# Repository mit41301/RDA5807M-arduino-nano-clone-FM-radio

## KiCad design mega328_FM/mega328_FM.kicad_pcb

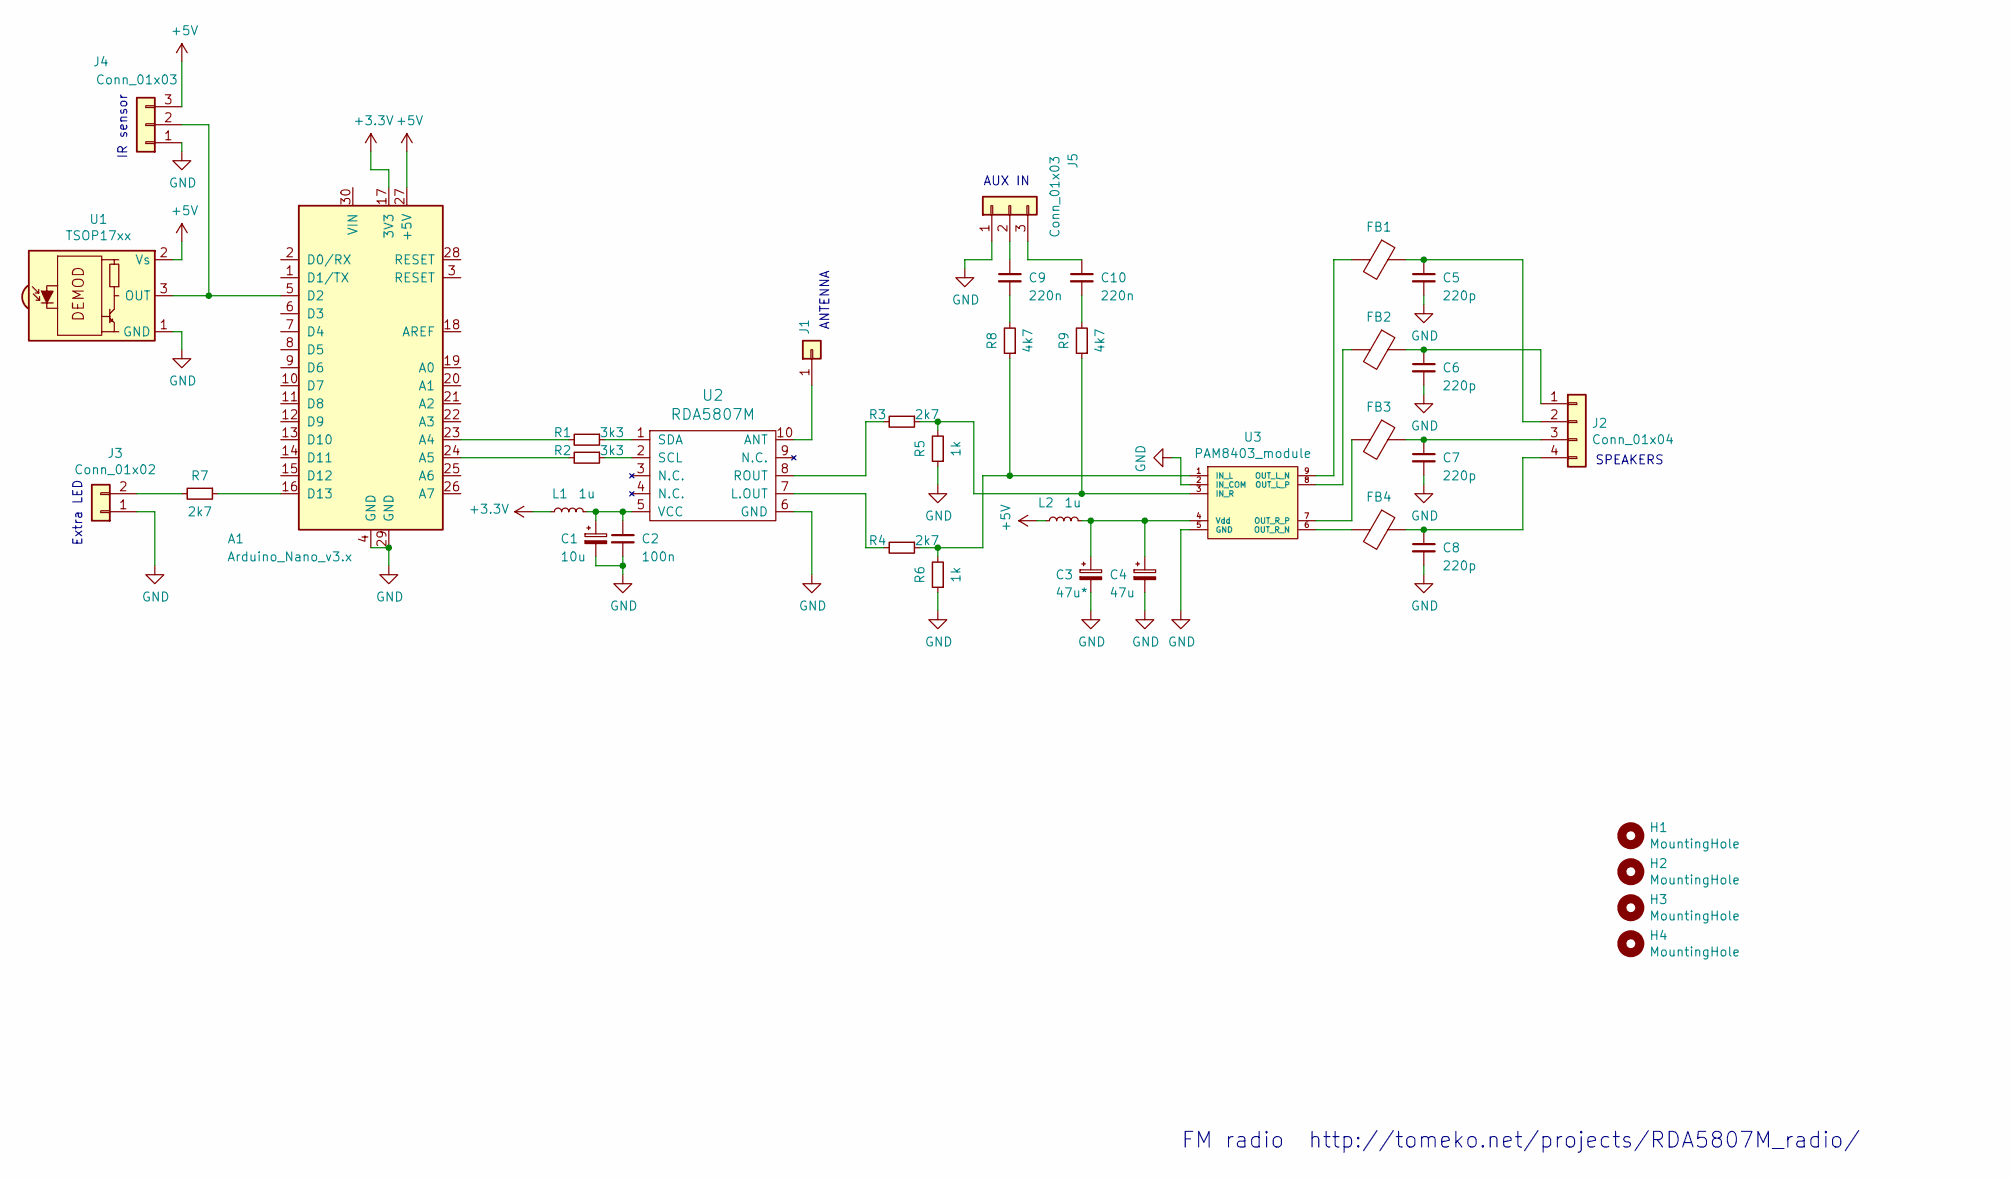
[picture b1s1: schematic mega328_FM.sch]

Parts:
A1: Arduino_Nano_v3.x; Arduino_Nano
C1: 10u; CP_Radial_D5.0mm_P2.50mm
C2: 100n; C_Disc_D5.0mm_W2.5mm_P5.00mm
C3: 47u*; CP_Radial_D7.5mm_P2.50mm
C4: 47u; CP_Radial_D7.5mm_P2.50mm
C5, C6, C7, C8: 220p; C_0805_2012Metric
C9, C10: 220n; C_Rect_L7.2mm_W3.5mm_P5.00mm_FKS2_FKP2_MKS2_MKP2
FB1, FB2, FB3, FB4: Ferrite_Bead; L_Axial_L9.5mm_D4.0mm_P12.70mm_Horizontal_Fastron_SMCC
H1, H2, H3, H4: MountingHole; MountingHole_3.2mm_M3
J1: Conn_01x01 ANTENNA; PinHeader_1x01_P2.54mm_Vertical
J2: Conn_01x04; PinHeader_1x04_P2.54mm_Vertical
J3: Conn_01x02; PinHeader_1x02_P2.54mm_Vertical
J4, J5: Conn_01x03; PinHeader_1x03_P2.54mm_Vertical
L1, L2: 1u; L_Axial_L7.0mm_D3.3mm_P10.16mm_Horizontal_Fastron_MICC
R1, R2: 3k3; R_Axial_DIN0207_L6.3mm_D2.5mm_P10.16mm_Horizontal
R3, R4, R7: 2k7; R_Axial_DIN0207_L6.3mm_D2.5mm_P10.16mm_Horizontal
R5, R6: 1k; R_Axial_DIN0207_L6.3mm_D2.5mm_P10.16mm_Horizontal
R8, R9: 4k7; R_Axial_DIN0207_L6.3mm_D2.5mm_P10.16mm_Horizontal
U1: TSOP17xx; Vishay_CAST-3Pin
U2: RDA5807M; RDA5807M_SMD
U3: PAM8403_module

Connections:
+3V3: A1.17 (3V3), L1.1
+5V: A1.27 (+5V), J4.3, L2.1, U1.2 (Vs)
GND: A1.4 (GND), A1.29 (GND), C1.2, C2.2, C3.2, C4.2, C5.2, C6.2, C7.2, C8.2, J3.1, J4.1, J5.1, R5.1, R6.1, U1.1 (GND), U2.6 (GND), U3.2 (IN_COM), U3.5 (GND)
unnamed: A1.5 (D2), J4.2, U1.3 (OUT)
unnamed: A1.16 (D13), R7.1
unnamed: A1.23 (A4), R1.2
unnamed: A1.24 (A5), R2.2
unnamed: C1.1, C2.1, L1.2, U2.5 (VCC)
unnamed: C3.1, C4.1, L2.2, U3.4 (Vdd)
unnamed: C5.1, FB1.1, J2.2
unnamed: C6.1, FB2.1, J2.1
unnamed: C7.1, FB3.1, J2.3
unnamed: C8.1, FB4.1, J2.4
unnamed: C9.1, J5.2
unnamed: C9.2, R8.2
unnamed: C10.1, J5.3
unnamed: C10.2, R9.2
unnamed: FB1.2, U3.9 (OUT_L_N)
unnamed: FB2.2, U3.8 (OUT_L_P)
unnamed: FB3.2, U3.7 (OUT_R_P)
unnamed: FB4.2, U3.6 (OUT_R_N)
unnamed: J1.1, U2.10 (ANT)
unnamed: J3.2, R7.2
unnamed: R1.1, U2.1 (SDA)
unnamed: R2.1, U2.2 (SCL)
unnamed: R3.1, R5.2, R9.1, U3.3 (IN_R)
unnamed: R3.2, U2.8 (ROUT)
unnamed: R4.1, R6.2, R8.1, U3.1 (IN_L)
unnamed: R4.2, U2.7 (L.OUT)

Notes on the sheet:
Extra LED
ANTENNA
SPEAKERS
IR sensor
AUX IN
FM radio http://tomeko.net/projects/RDA5807M_radio/

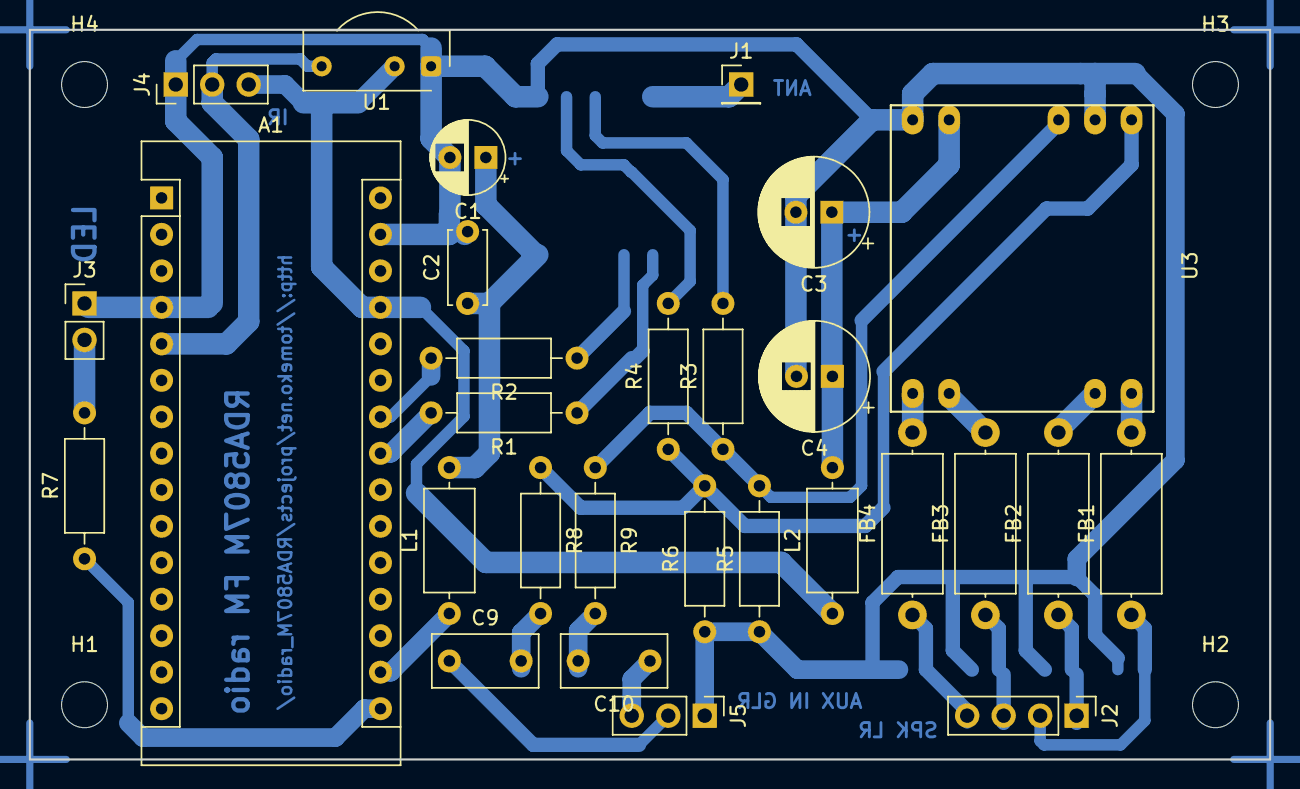
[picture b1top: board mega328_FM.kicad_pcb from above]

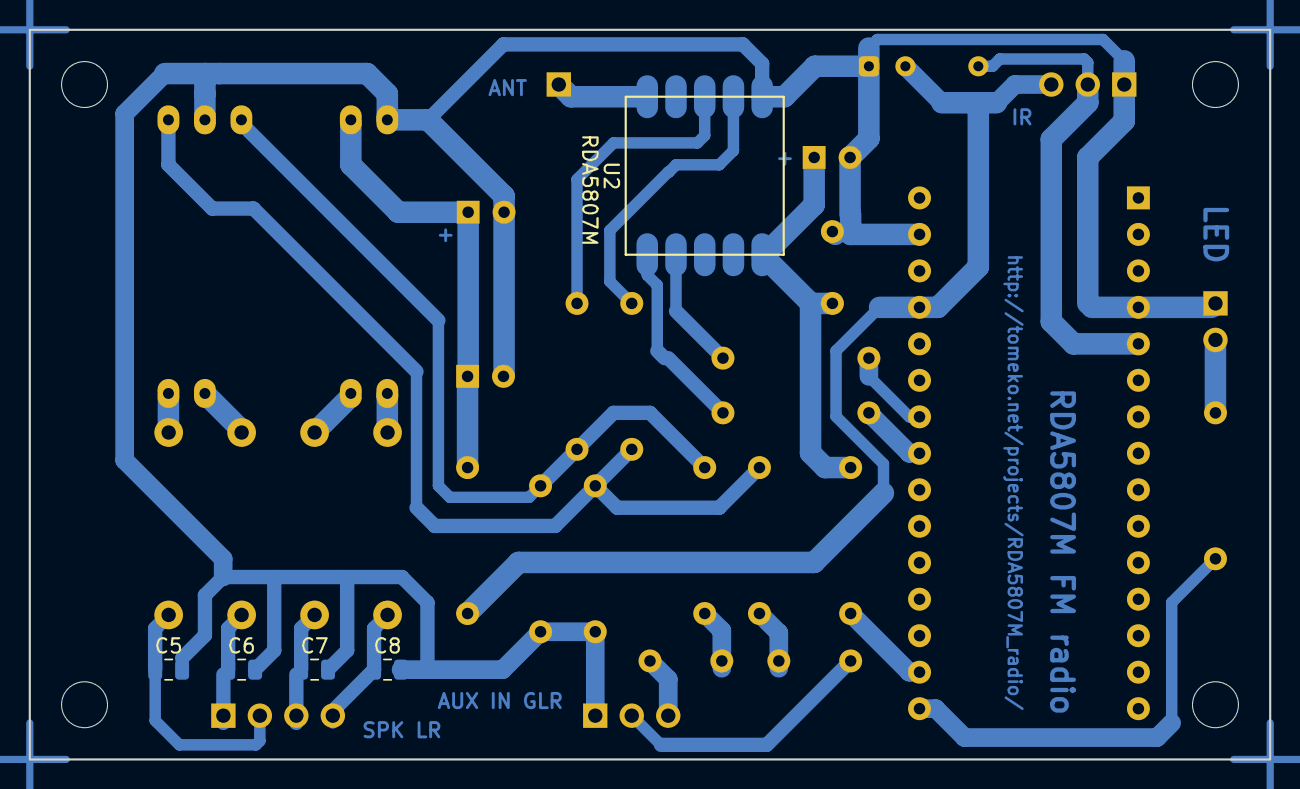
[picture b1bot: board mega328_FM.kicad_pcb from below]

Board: 2 copper layers, 86.4 x 50.8 mm, 38 parts (5 on the bottom side), 29 nets.

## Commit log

2024-07-28 Initial uploads
2025-11-18 KiCAD
2025-11-18 ATmega 328 SW
2025-12-01 mega328_FM_20190223
2025-12-01 ATMega328_FM_20190223
